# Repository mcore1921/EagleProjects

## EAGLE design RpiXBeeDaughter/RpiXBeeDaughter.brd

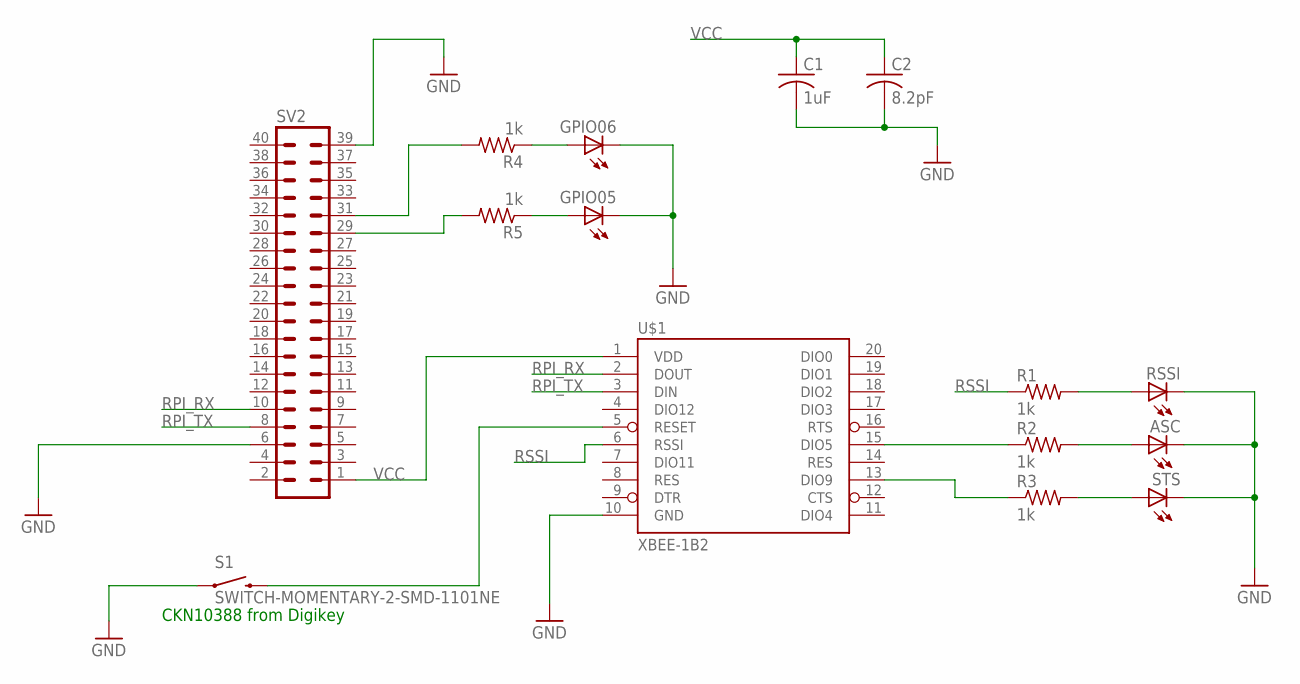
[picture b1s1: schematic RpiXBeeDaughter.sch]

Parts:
ASC: LEDCHIP-LED0603; CHIP-LED0603
C1: 1uF; C0805
C2: 8.2pF; C0603
GPIO05, GPIO06: LEDCHIP-LED0603; CHIP-LED0603
R1, R2, R3, R4, R5: 1k; R0603
RSSI: LEDCHIP-LED0603; CHIP-LED0603
S1: SWITCH-MOMENTARY-2-SMD-1101NE; TACTILE-SWITCH-1101NE
STS: LEDCHIP-LED0603; CHIP-LED0603
SV2: MA20-2
U$1: XBEE-1B2; XBEE-SILK

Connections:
GND: ASC.C, C1.2, C2.2, GPIO05.C, GPIO06.C, RSSI.C, S1.P$1 (1), STS.C, SV2.6, SV2.39, U$1.10 (GND)
unnamed: S1.P$2 (2), U$1.5 (RESET)
unnamed: R3.2, STS.A
unnamed: R2.1, U$1.15 (DIO5)
unnamed: R1.2, RSSI.A
unnamed: ASC.A, R2.2
unnamed: R3.1, U$1.13 (DIO9)
unnamed: R4.2, SV2.31
unnamed: GPIO06.A, R4.1
unnamed: R5.2, SV2.29
unnamed: GPIO05.A, R5.1
RPI_RX: SV2.10, U$1.2 (DOUT)
RPI_TX: SV2.8, U$1.3 (DIN)
RSSI: R1.1, U$1.6 (RSSI)
VCC: C1.1, C2.1, SV2.1, U$1.1 (VDD)

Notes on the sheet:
CKN10388 from Digikey

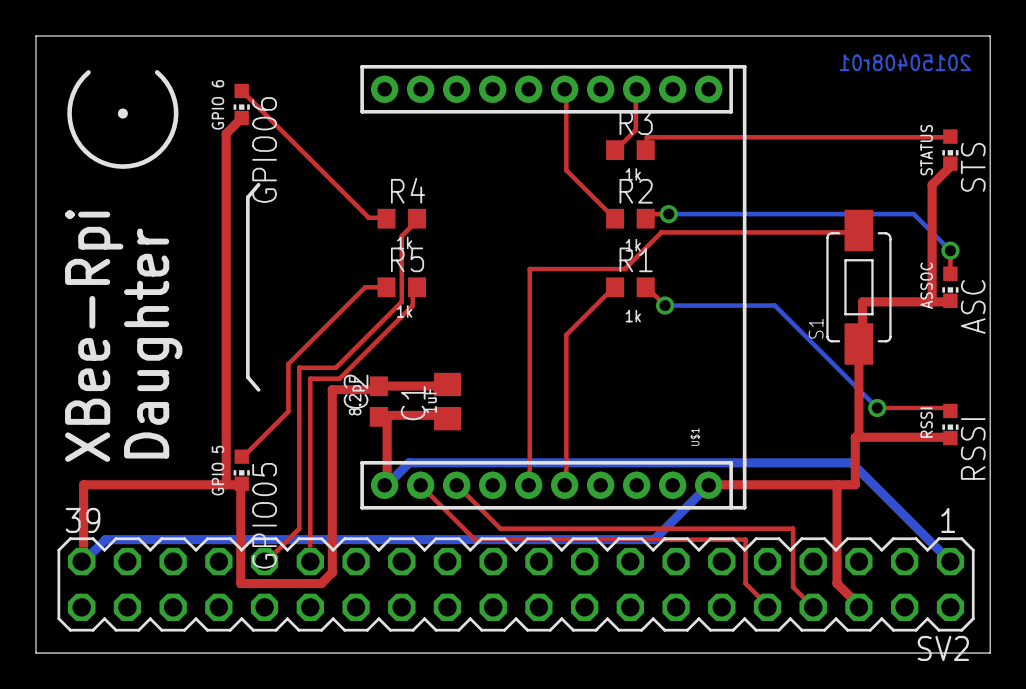
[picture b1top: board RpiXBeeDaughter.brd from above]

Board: 2 copper layers, 53.0 x 34.3 mm, 15 parts (0 on the bottom side), 15 nets.

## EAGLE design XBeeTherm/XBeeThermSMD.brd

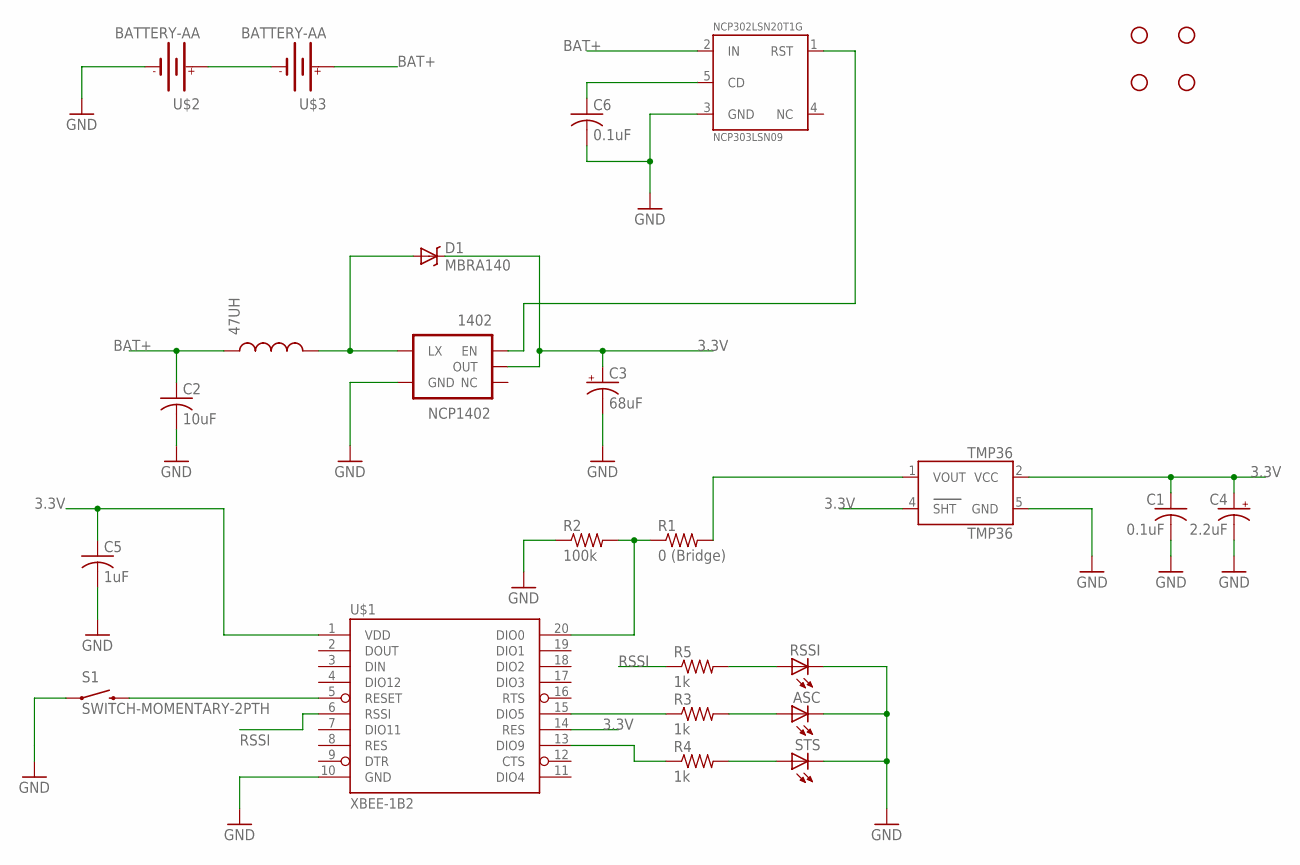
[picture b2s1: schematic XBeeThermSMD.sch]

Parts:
47UH: INDUCTORCR54; CR54
1402: NCP1402; SOT23-5
ASC: LEDCHIP-LED0603; CHIP-LED0603
C1, C6: 0.1uF; C0402
C2: 10uF; C0805
C3: 68uF; CT3216
C4: 2.2uF; R/2012-12R
C5: 1uF; C0805
D1: MBRA140; SMA-DIODE
NCP302LSN20T1G: NCP303LSN09; SOT23-5
R1: 0 (Bridge); R0603
R2: 100k; R0603
R3, R4, R5: 1k; R0603
RSSI: LEDCHIP-LED0603; CHIP-LED0603
S1: SWITCH-MOMENTARY-2PTH; TACTILE-PTH
STANDOFF1, STANDOFF2, STANDOFF3, STANDOFF4: STAND-OFF
STS: LEDCHIP-LED0603; CHIP-LED0603
TMP36: TMP36; SOT23-5
U$1: XBEE-1B2; XBEE-SILK
U$2, U$3: BATTERY-AA; BATTERY_AA_CLIPS

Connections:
3.3V: 1402.2 (OUT), C1.1, C3.+, C4.+, C5.1, D1.C, TMP36.2 (VCC), TMP36.4 (SHT), U$1.1 (VDD), U$1.14 (RES)
BAT+: 47UH.P$1 (1), C2.1, NCP302LSN20T1G.2 (IN), U$3.PWR@1 (+), U$3.PWR@2 (+)
GND: 1402.4 (GND), ASC.C, C1.2, C2.2, C3.-, C4.-, C5.2, C6.2, NCP302LSN20T1G.3 (GND), R2.1, RSSI.C, S1.1, STS.C, TMP36.5 (GND), U$1.10 (GND), U$2.GND@1 (-), U$2.GND@2 (-)
unnamed: 47UH.P$2 (2), 1402.5 (LX), D1.A
unnamed: U$2.PWR@1 (+), U$2.PWR@2 (+), U$3.GND@1 (-), U$3.GND@2 (-)
unnamed: R1.1, R2.2, U$1.20 (DIO0)
unnamed: R1.2, TMP36.1 (VOUT)
unnamed: R3.1, U$1.15 (DIO5)
unnamed: R4.1, U$1.13 (DIO9)
unnamed: ASC.A, R3.2
unnamed: R4.2, STS.A
unnamed: S1.3 (2), U$1.5 (RESET)
unnamed: C6.1, NCP302LSN20T1G.5 (CD)
unnamed: 1402.1 (EN), NCP302LSN20T1G.1 (RST)
unnamed: R5.2, RSSI.A
RSSI: R5.1, U$1.6 (RSSI)

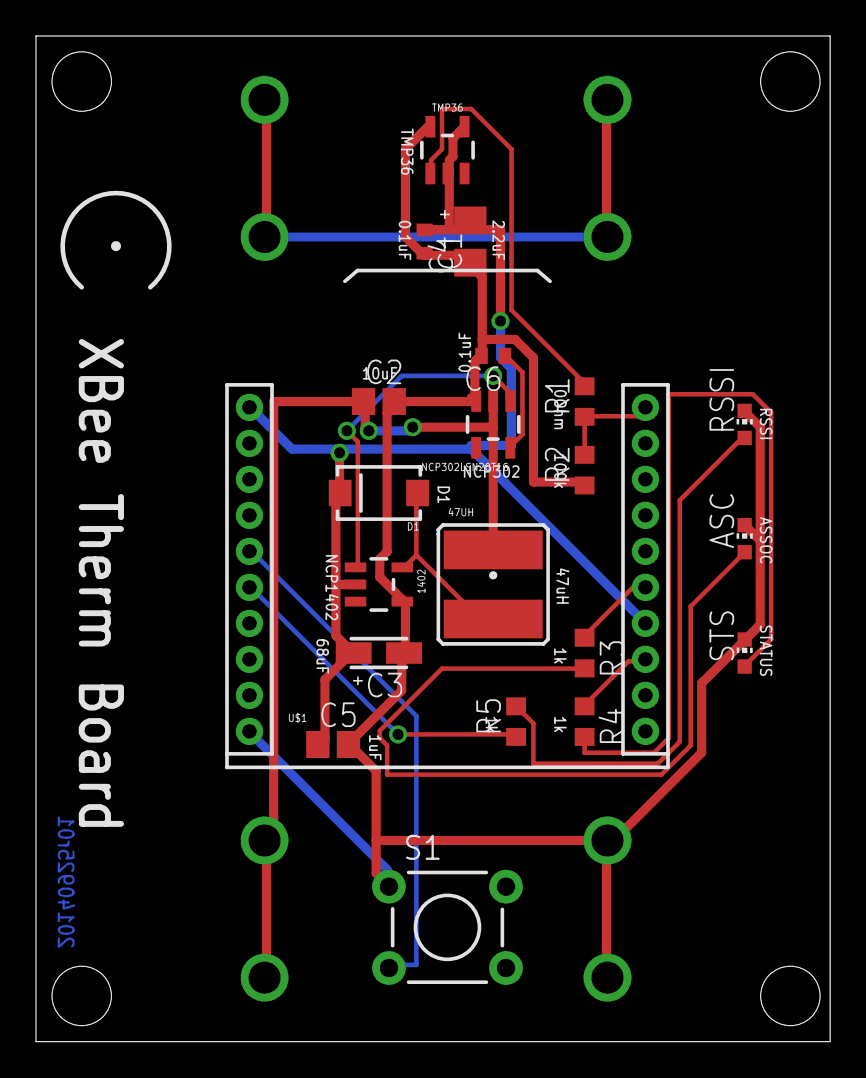
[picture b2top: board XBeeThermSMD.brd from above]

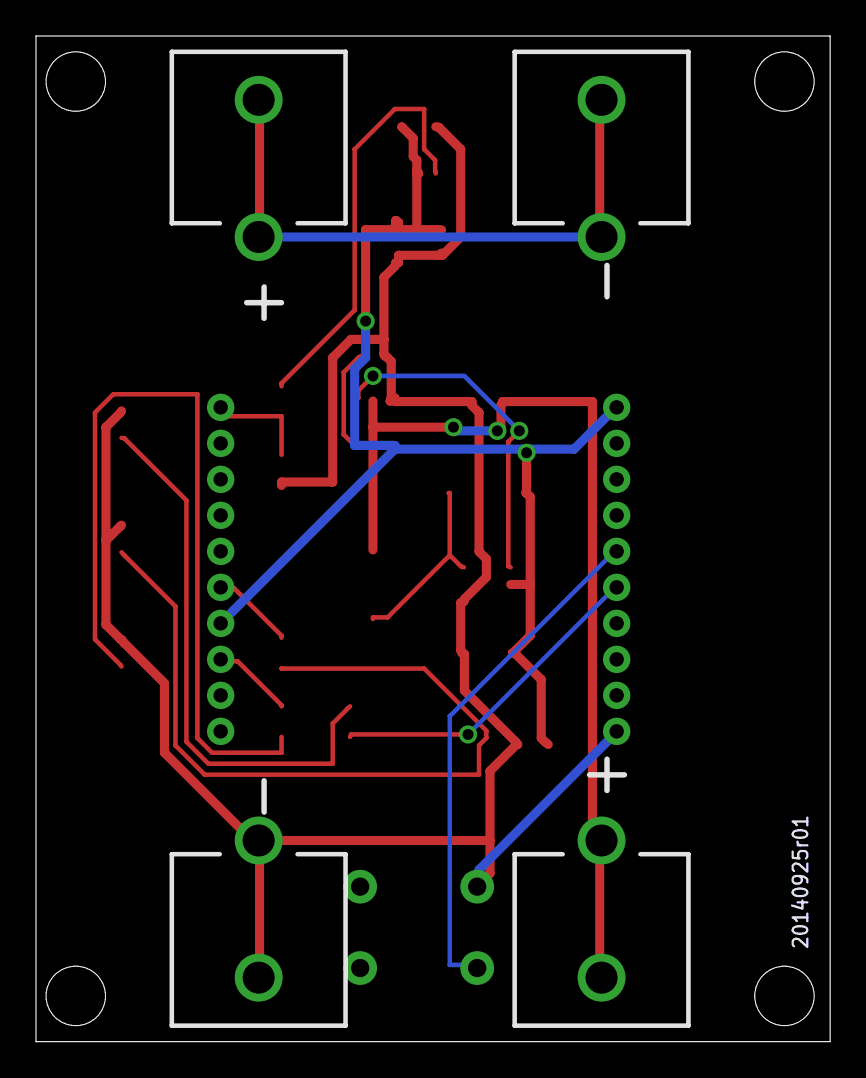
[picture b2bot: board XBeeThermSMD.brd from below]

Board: 2 copper layers, 44.1 x 55.9 mm, 27 parts (2 on the bottom side), 16 nets.

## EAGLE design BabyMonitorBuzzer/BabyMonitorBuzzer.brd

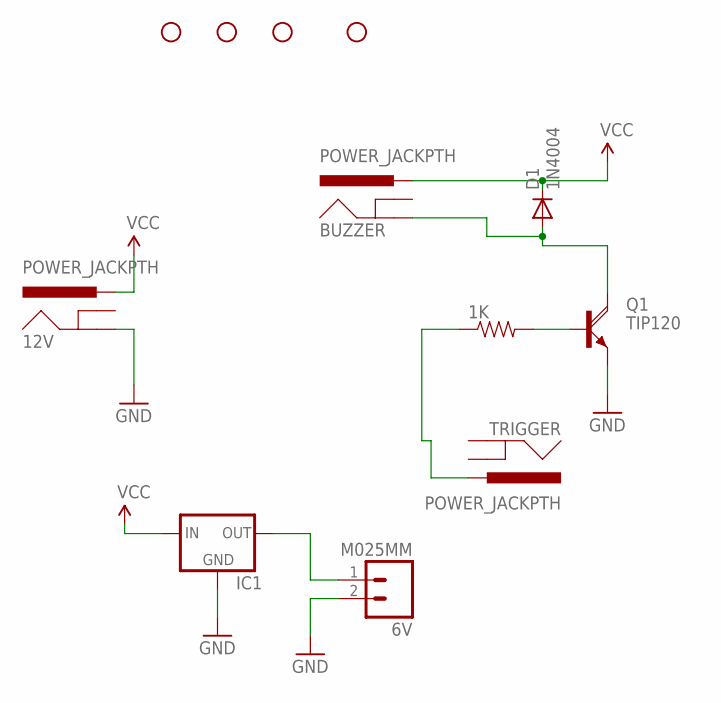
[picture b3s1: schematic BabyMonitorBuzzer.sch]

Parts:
1K: RESISTORAXIAL-0.3; AXIAL-0.3
6V: M025MM; SCREWTERMINAL-5MM-2
12V: POWER_JACKPTH; POWER_JACK_PTH
BUZZER: POWER_JACKPTH; POWER_JACK_PTH
D1: 1N4004; DO41-10
IC1: 78XXL
Q1: TIP120; TO220AH
STANDOFF1, STANDOFF2, STANDOFF3, STANDOFF4: STAND-OFF
TRIGGER: POWER_JACKPTH; POWER_JACK_PTH

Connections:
GND: 6V.2, 12V.GND, IC1.GND, Q1.E
unnamed: 1K.P$2 (2), Q1.B
unnamed: BUZZER.GND, D1.A, Q1.C
unnamed: 1K.P$1 (1), TRIGGER.PWR
unnamed: 6V.1, IC1.OUT
VCC: 12V.PWR, BUZZER.PWR, D1.C, IC1.IN

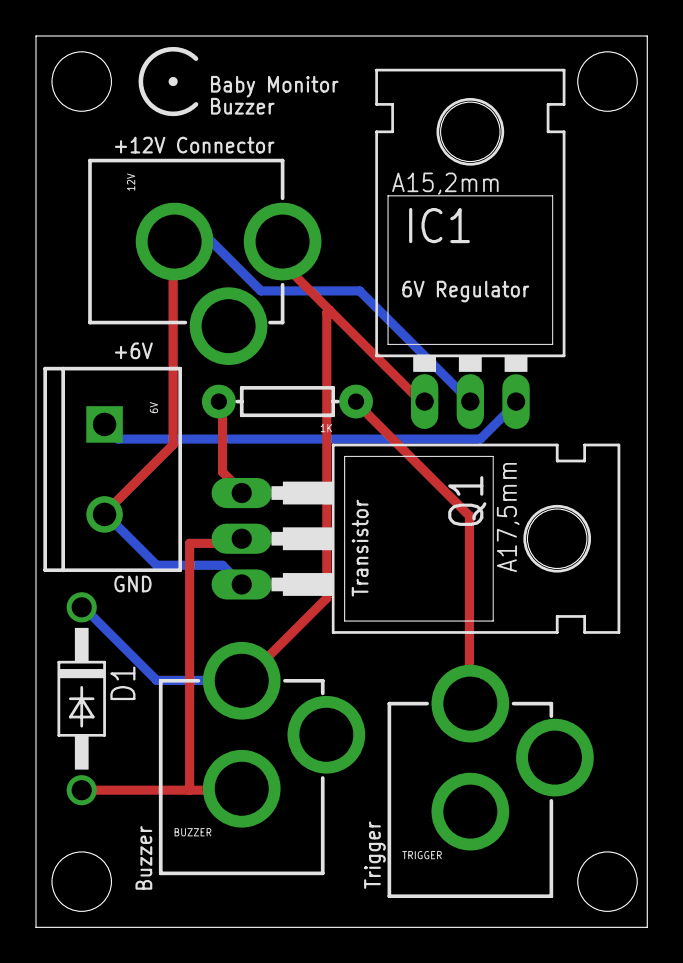
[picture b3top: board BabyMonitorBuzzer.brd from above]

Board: 2 copper layers, 34.0 x 49.5 mm, 12 parts (0 on the bottom side), 6 nets.

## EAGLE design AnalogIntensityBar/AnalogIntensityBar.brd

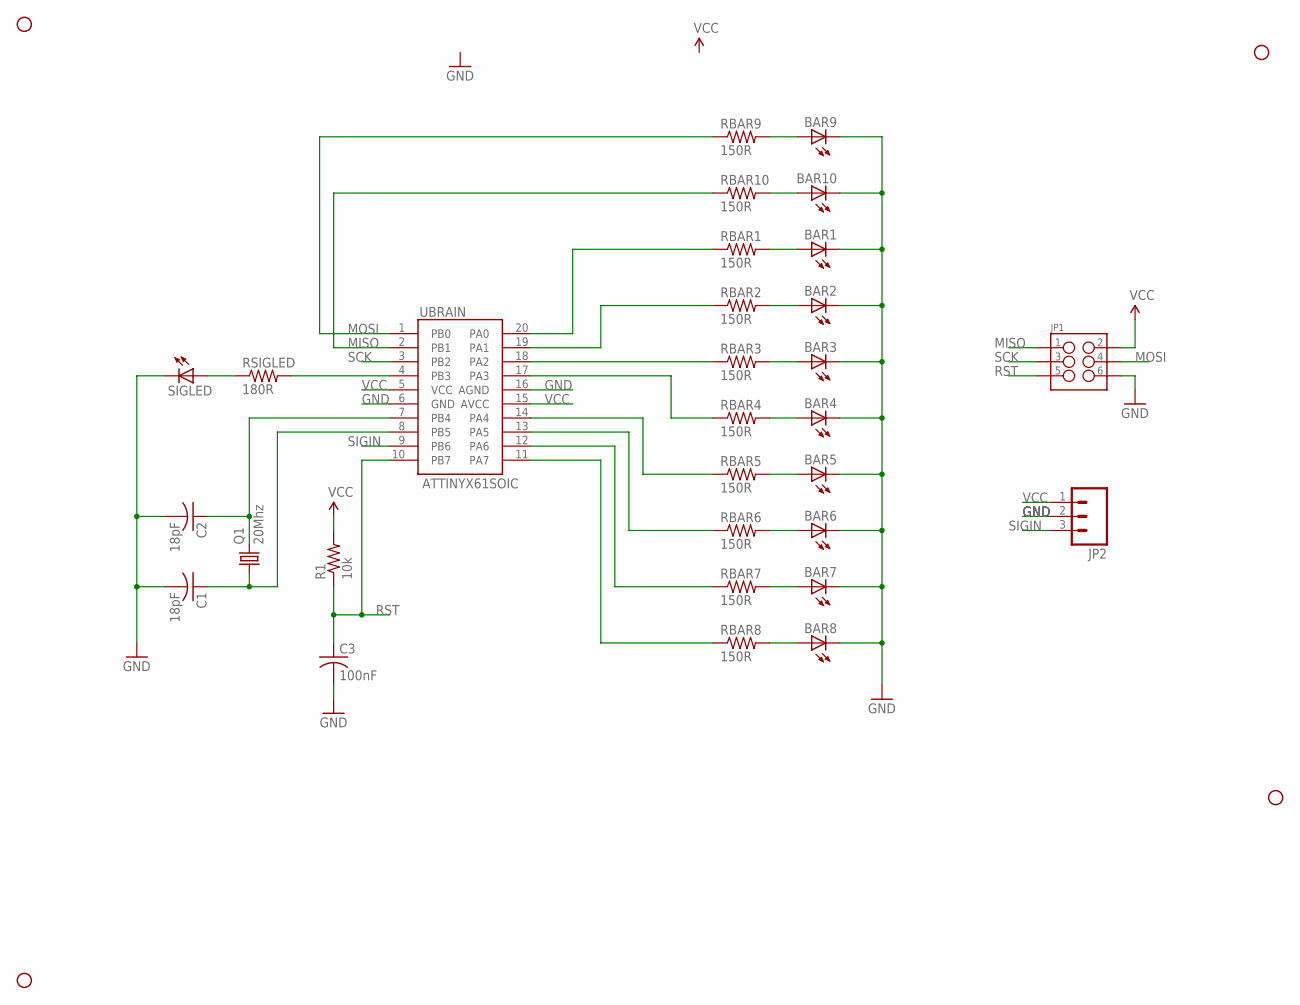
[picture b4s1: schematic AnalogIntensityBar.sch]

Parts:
BAR1, BAR2, BAR3, BAR4, BAR5, BAR6, BAR7, BAR8, BAR9, BAR10: LEDCHIP-LED0603; CHIP-LED0603
C1, C2: 18pF; C0402
C3: 100nF; C0402
JP1: M03X22X3_SILK_SM; 2X3
JP2: M03PTH; 1X03
Q1: 20Mhz; HC49UP
R1: 10k; R0402
RBAR1, RBAR2, RBAR3, RBAR4, RBAR5, RBAR6, RBAR7, RBAR8, RBAR9, RBAR10: 150R; R0603
RSIGLED: 180R; R0603
SIGLED: LEDCHIP-LED0805; CHIP-LED0805
STANDOFF1, STANDOFF2, STANDOFF3, STANDOFF4: STAND-OFF
UBRAIN: ATTINYX61SOIC; 20S2

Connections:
GND: BAR1.C, BAR2.C, BAR3.C, BAR4.C, BAR5.C, BAR6.C, BAR7.C, BAR8.C, BAR9.C, BAR10.C, C1.2, C2.2, C3.2, JP1.6, JP2.2, SIGLED.C, UBRAIN.6 (GND), UBRAIN.16 (AGND)
MISO: JP1.1, RBAR10.1, UBRAIN.2 (PB1)
MOSI: JP1.4, RBAR9.1, UBRAIN.1 (PB0)
unnamed: RBAR1.1, UBRAIN.20 (PA0)
unnamed: RBAR2.1, UBRAIN.19 (PA1)
unnamed: C1.1, Q1.1, UBRAIN.8 (PB5)
unnamed: C2.1, Q1.2, UBRAIN.7 (PB4)
unnamed: RBAR3.1, UBRAIN.18 (PA2)
unnamed: RBAR4.1, UBRAIN.17 (PA3)
unnamed: RBAR5.1, UBRAIN.14 (PA4)
unnamed: RBAR6.1, UBRAIN.13 (PA5)
unnamed: RBAR7.1, UBRAIN.12 (PA6)
unnamed: RBAR8.1, UBRAIN.11 (PA7)
unnamed: BAR1.A, RBAR1.2
unnamed: BAR2.A, RBAR2.2
unnamed: BAR3.A, RBAR3.2
unnamed: BAR4.A, RBAR4.2
unnamed: BAR5.A, RBAR5.2
unnamed: BAR6.A, RBAR6.2
unnamed: BAR7.A, RBAR7.2
unnamed: BAR8.A, RBAR8.2
unnamed: RSIGLED.2, UBRAIN.4 (PB3)
unnamed: RSIGLED.1, SIGLED.A
unnamed: BAR9.A, RBAR9.2
unnamed: BAR10.A, RBAR10.2
RST: C3.1, JP1.5, R1.1, UBRAIN.10 (PB7)
SCK: JP1.3, UBRAIN.3 (PB2)
SIGIN: JP2.3, UBRAIN.9 (PB6)
VCC: JP1.2, JP2.1, R1.2, UBRAIN.5 (VCC), UBRAIN.15 (AVCC)

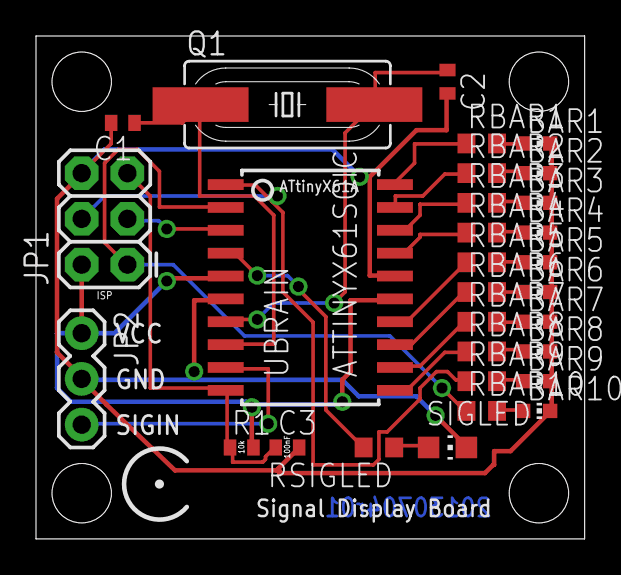
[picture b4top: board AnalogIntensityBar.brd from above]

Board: 2 copper layers, 30.5 x 27.9 mm, 34 parts (0 on the bottom side), 29 nets.

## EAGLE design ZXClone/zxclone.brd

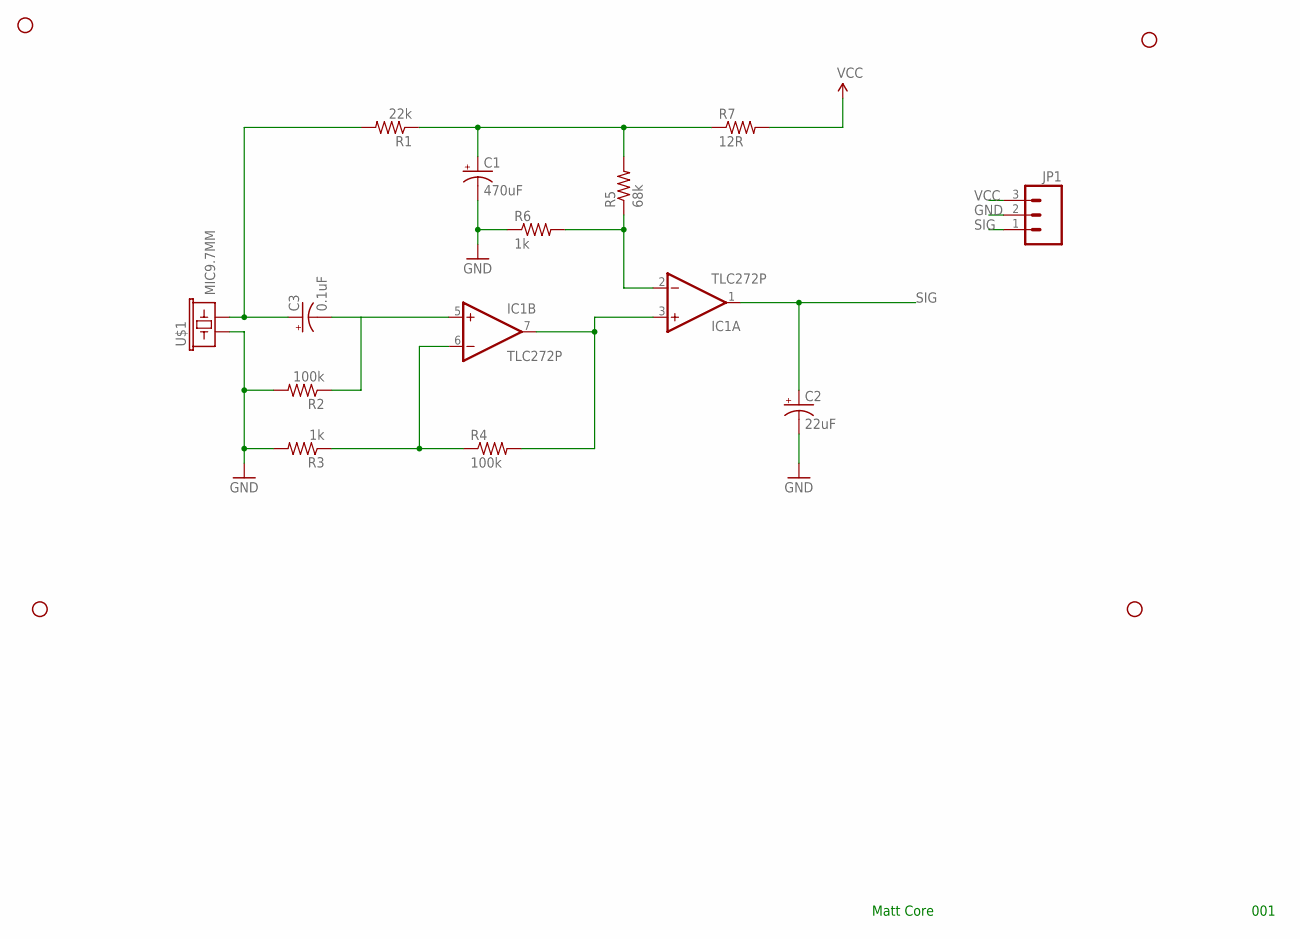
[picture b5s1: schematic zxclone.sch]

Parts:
C1: 470uF; E2,5-7
C2: 22uF; E5-4
C3: 0.1uF; E1,8-4
IC1: TLC272P; DIL08
JP1: M03PTH; 1X03
R1: 22k; 0207/10
R2, R4: 100k; 0207/10
R3, R6: 1k; 0207/10
R5: 68k; 0207/10
R7: 12R; 0207/10
STANDOFF1, STANDOFF2, STANDOFF3, STANDOFF4: STAND-OFF
U$1: MIC9.7MM; MIC-9.7MM

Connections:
GND: C1.-, C2.-, JP1.2, R2.2, R3.2, R6.1, U$1.1
unnamed: C1.+, R1.1, R5.2, R7.1
unnamed: IC1.2 (-IN), R5.1, R6.2
unnamed: IC1.3 (+IN), IC1.7 (OUT), R4.2
unnamed: IC1.6 (-IN), R3.1, R4.1
unnamed: C3.-, IC1.5 (+IN), R2.1
unnamed: C3.+, R1.2, U$1.2
SIG: C2.+, IC1.1 (OUT), JP1.1
V+: IC1.8 (V+)
V-: IC1.4 (V-)
VCC: JP1.3, R7.2

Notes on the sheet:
Matt Core
001

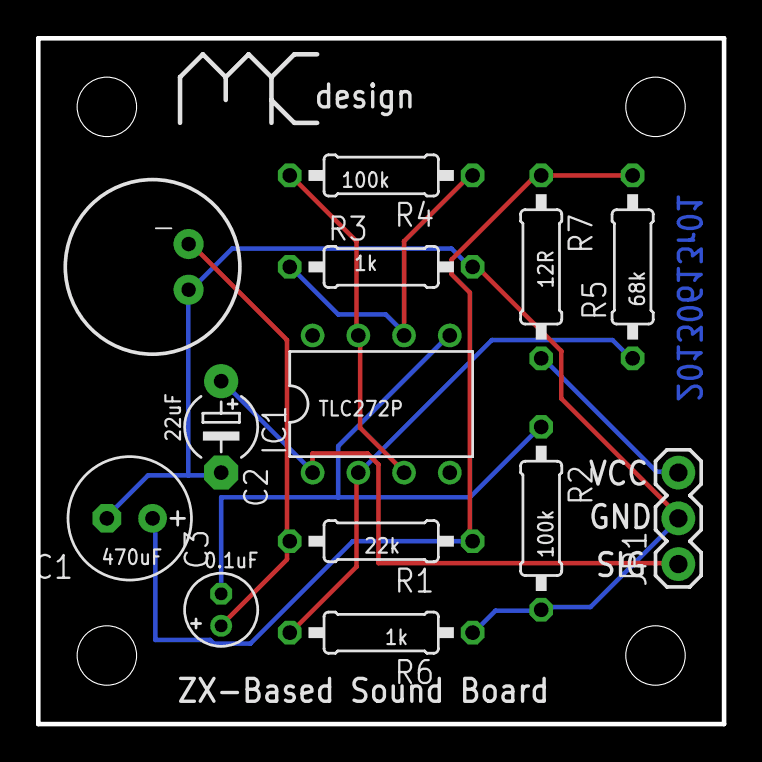
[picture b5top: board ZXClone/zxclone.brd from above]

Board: 2 copper layers, 38.1 x 38.1 mm, 17 parts (0 on the bottom side), 9 nets.

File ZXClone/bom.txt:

Partlist exported from C:/Users/Matt/Documents/eagle/ZXClone/zxclone.sch at 7/21/2013 9:11:37 PM

Part      Value     Device        Package   Description                                                    
C1        470uF     CPOL-USE2.5-7 E2,5-7    POLARIZED CAPACITOR, American symbol                           
C2        22uF      CPOL-USE5-4   E5-4      POLARIZED CAPACITOR, American symbol                           
C3        0.1uF     CPOL-USE1.8-4 E1,8-4    POLARIZED CAPACITOR, American symbol                           
IC1       TLC272P   TLC272P       DIL08     OP AMP                                                         
JP1                 M03PTH        1X03      Header 3                                                       
R1        22k       R-US_0207/10  0207/10   RESISTOR, American symbol                                      
R2        100k      R-US_0207/10  0207/10   RESISTOR, American symbol                                      
R3        1k        R-US_0207/10  0207/10   RESISTOR, American symbol                                      
R4        100k      R-US_0207/10  0207/10   RESISTOR, American symbol                                      
R5        68k       R-US_0207/10  0207/10   RESISTOR, American symbol                                      
R6        1k        R-US_0207/10  0207/10   RESISTOR, American symbol                                      
R7        12R       R-US_0207/10  0207/10   RESISTOR, American symbol                                      
STANDOFF1 STAND-OFF STAND-OFF     STAND-OFF #4 Stand Off                                                   
STANDOFF2 STAND-OFF STAND-OFF     STAND-OFF #4 Stand Off                                                   
STANDOFF3 STAND-OFF STAND-OFF     STAND-OFF #4 Stand Off                                                   
STANDOFF4 STAND-OFF STAND-OFF     STAND-OFF #4 Stand Off                                                   
U$1       MIC9.7MM  MIC9.7MM      MIC-9.7MM Omni-directional electret microphone. 9.7mm standard diameter.

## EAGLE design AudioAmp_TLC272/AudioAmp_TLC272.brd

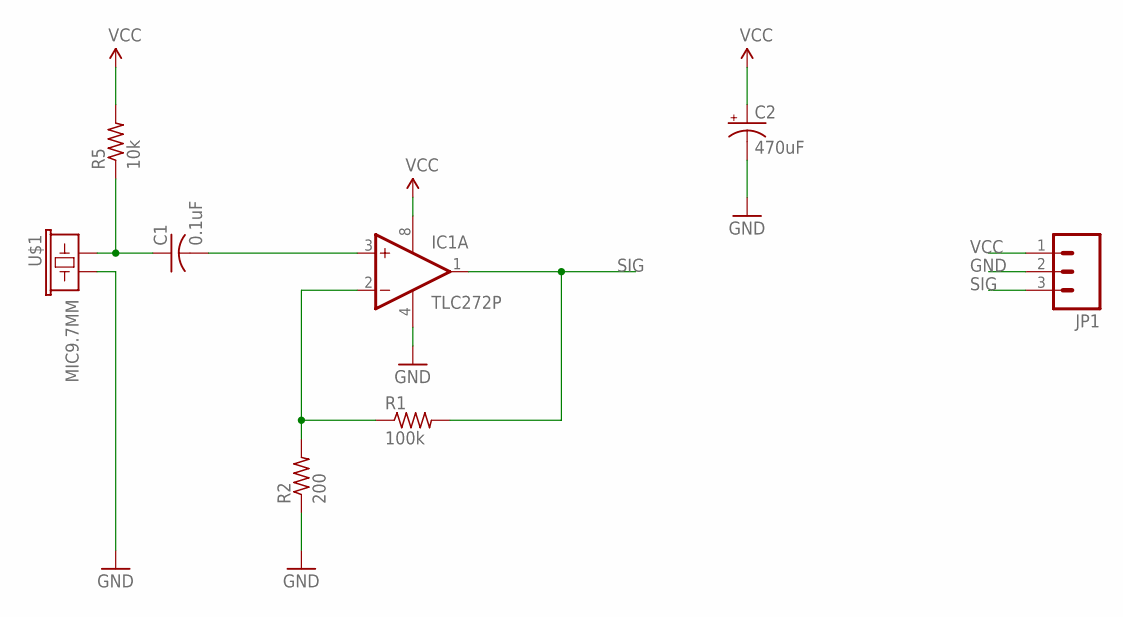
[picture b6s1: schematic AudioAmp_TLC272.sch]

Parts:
C1: 0.1uF; C025-025X050
C2: 470uF; E2,5-7
IC1: TLC272P; DIL08
JP1: M03PTH; 1X03
R1: 100k; 0207/10
R2: 200; 0207/10
R5: 10k; 0207/10
U$1: MIC9.7MM; MIC-9.7MM

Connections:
GND: C2.-, IC1.4 (V-), JP1.2, R2.1, U$1.2
unnamed: C1.1, R5.1, U$1.1
unnamed: C1.2, IC1.3 (+IN)
unnamed: IC1.2 (-IN), R1.1, R2.2
SIG: IC1.1 (OUT), JP1.3, R1.2
VCC: C2.+, IC1.8 (V+), JP1.1, R5.2

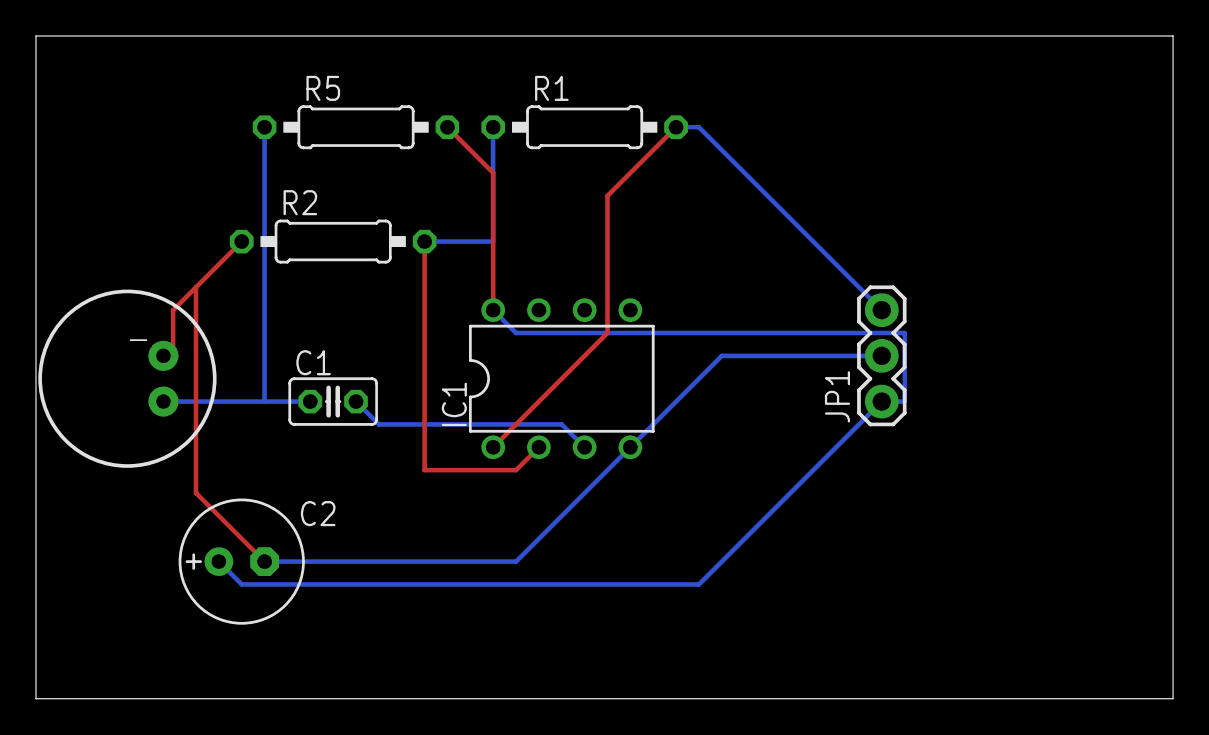
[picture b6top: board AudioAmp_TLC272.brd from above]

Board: 2 copper layers, 63.2 x 36.8 mm, 8 parts (0 on the bottom side), 6 nets.

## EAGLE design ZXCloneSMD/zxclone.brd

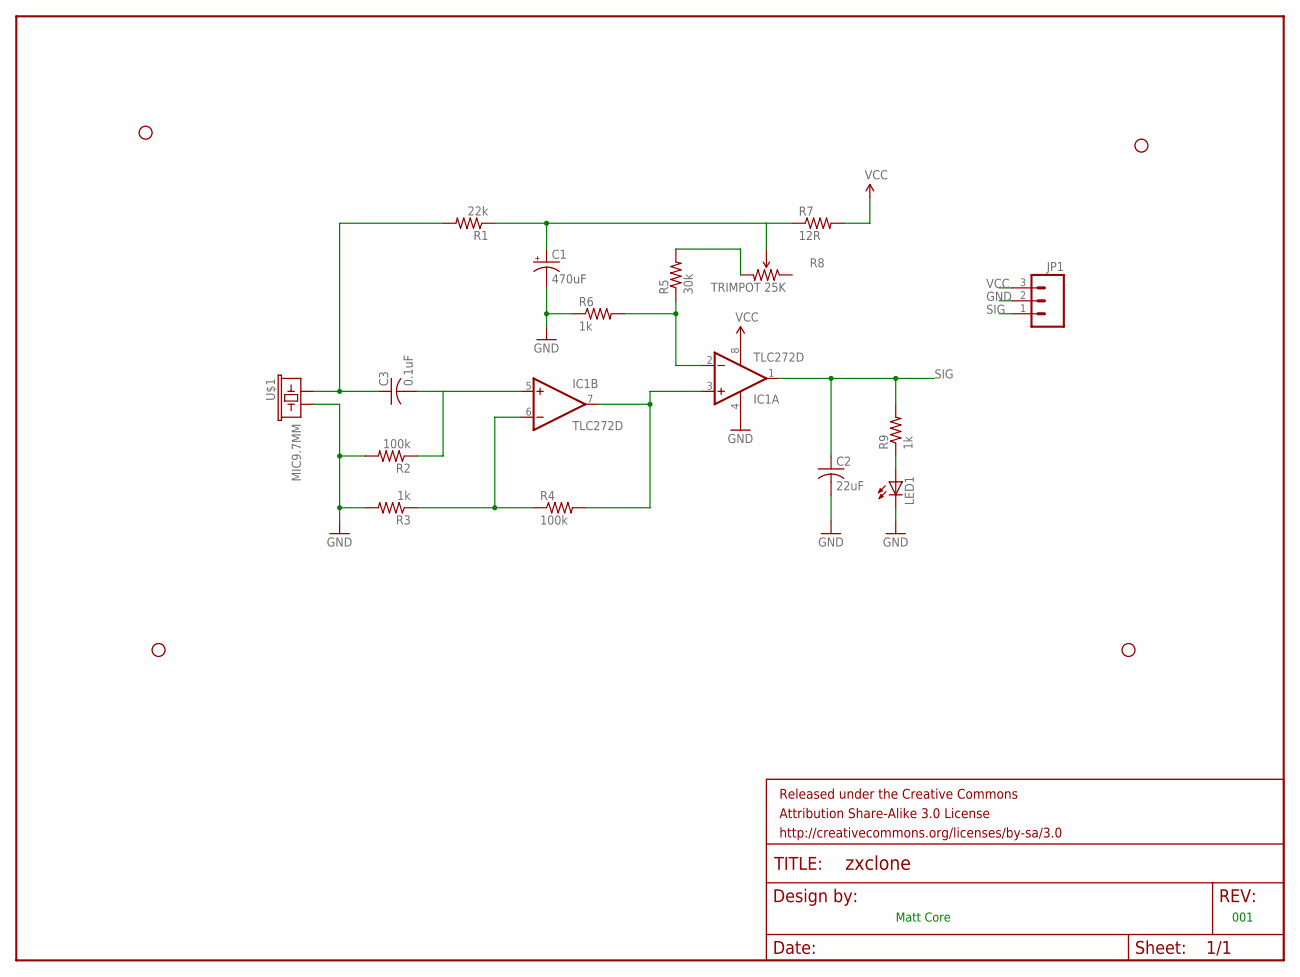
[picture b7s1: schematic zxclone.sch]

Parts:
C1: 470uF; E2,5-7
C2: 22uF; C1206
C3: 0.1uF; C1005
FRAME1: FRAME-LETTER; CREATIVE_COMMONS
IC1: TLC272D; SO08
JP1: M03PTH; 1X03
LED1: LEDSML0603; SML0603
R1: 22k; R0402
R2, R4: 100k; R0402
R3, R6, R9: 1k; R0402
R5: 30k; R0402
R7: 12R; R0805
R8: TRIMPOT 25K; TRIMPOT_TC33
STANDOFF1, STANDOFF2, STANDOFF3, STANDOFF4: STAND-OFF
U$1: MIC9.7MM; MIC-9.7MM

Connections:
GND: C1.-, C2.2, IC1.4 (V-), JP1.2, LED1.C, R2.2, R3.2, R6.1, U$1.2
unnamed: C1.+, R1.1, R7.1, R8.2 (WIPER)
unnamed: IC1.2 (-IN), R5.1, R6.2
unnamed: IC1.3 (+IN), IC1.7 (OUT), R4.2
unnamed: IC1.6 (-IN), R3.1, R4.1
unnamed: C3.2, IC1.5 (+IN), R2.1
unnamed: R5.2, R8.3 (CW)
unnamed: C3.1, R1.2, U$1.1
unnamed: LED1.A, R9.1
SIG: C2.1, IC1.1 (OUT), JP1.1, R9.2
VCC: IC1.8 (V+), JP1.3, R7.2

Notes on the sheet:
Matt Core
001

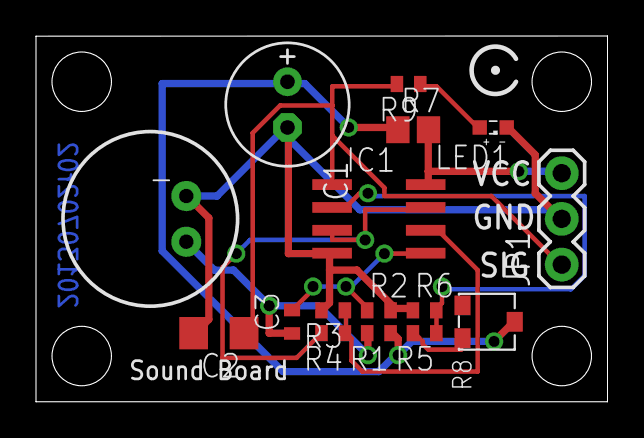
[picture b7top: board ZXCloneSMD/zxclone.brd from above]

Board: 2 copper layers, 31.8 x 20.3 mm, 21 parts (0 on the bottom side), 11 nets.

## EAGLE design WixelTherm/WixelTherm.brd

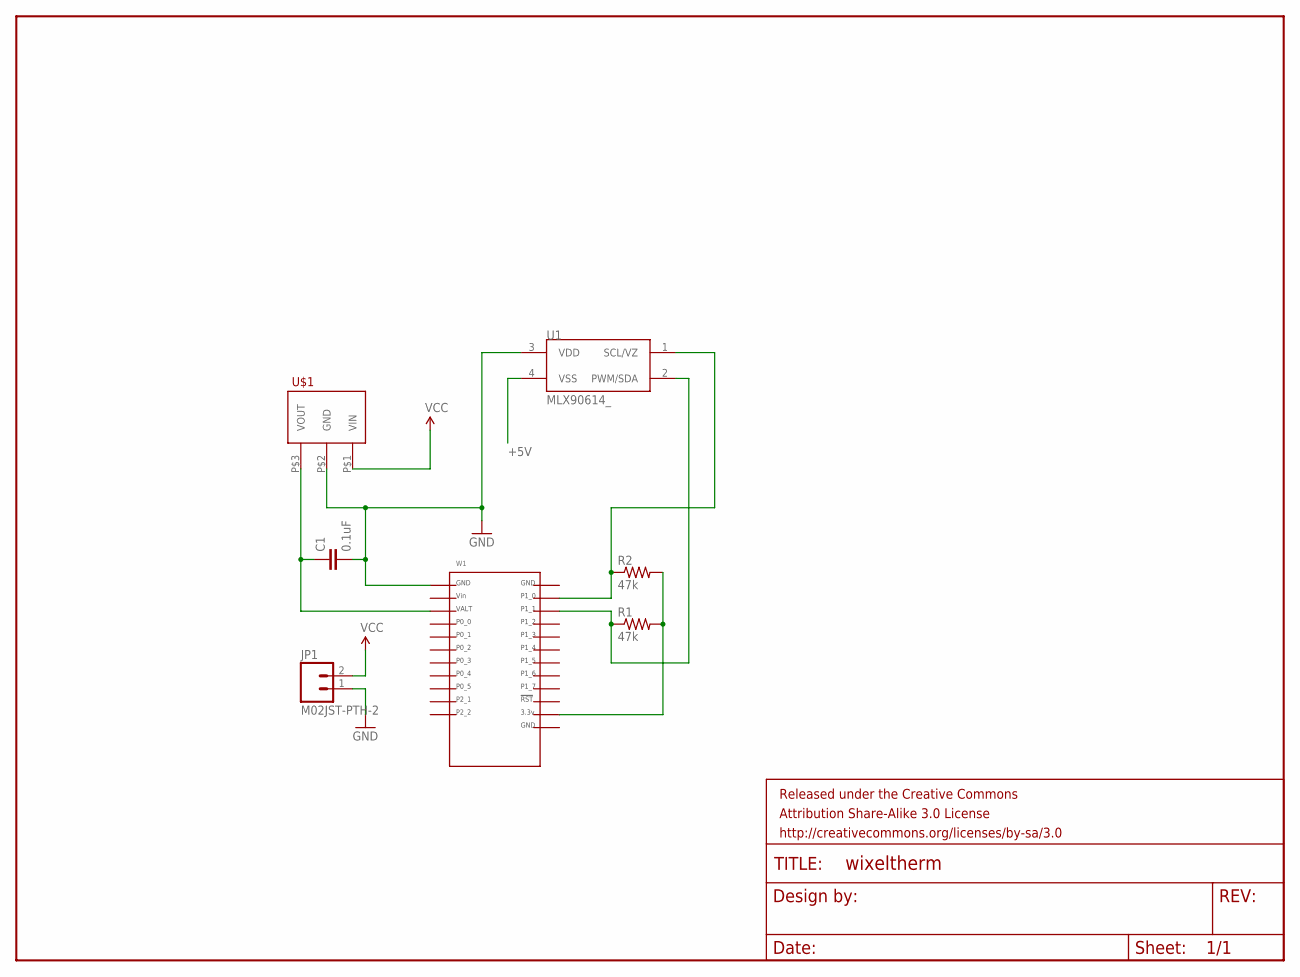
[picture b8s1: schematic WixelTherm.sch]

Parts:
C1: 0.1uF; 0603-CAP
FRAME1: FRAME-LETTER; CREATIVE_COMMONS
JP1: M02JST-PTH-2; JST-2-PTH
R1, R2: 47k; 0207/10
U1: MLX90614_; TO-39
U$1: POLOLU_NCP1402; POLOLU_BREAKOUT
W1: WIXEL

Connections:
+5V: C1.1, U1.4 (VSS), U$1.P$3 (VOUT), W1.P$3
GND: C1.2, JP1.1, U1.3 (VDD), U$1.P$2 (GND), W1.P$1
unnamed: R1.1, U1.2 (PWM/SDA), W1.P$14
unnamed: R1.2, R2.2, W1.P$22
unnamed: R2.1, U1.1 (SCL/VZ), W1.P$13
VCC: JP1.2, U$1.P$1 (VIN)

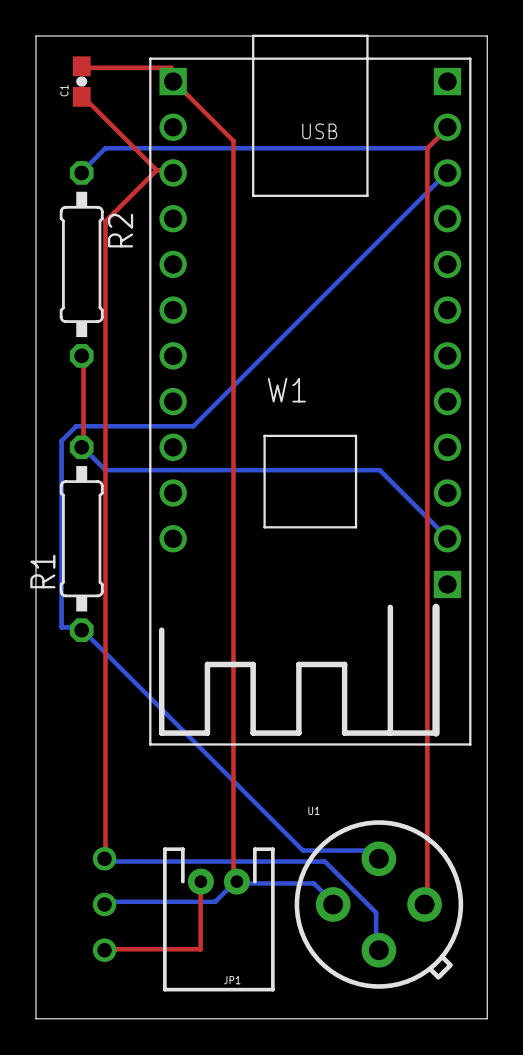
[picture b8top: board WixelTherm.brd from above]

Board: 2 copper layers, 25.1 x 54.6 mm, 8 parts (0 on the bottom side), 6 nets.

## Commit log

2013-06-06 creation
2013-06-12 interim checkin while building schematic
2013-06-12 interim checkin while building zxclone
2013-06-12 another initial rev
2013-06-12 Ready to send gerber files
2013-06-12 revision sent for first fab
2013-06-13 first rev of smd version
2013-07-02 On the way to a second proto board
2013-07-02 Some file cleanup
2013-07-02 Working revision with LED and trimpot
2013-07-03 Second submission for fab to osh park
2013-07-05 First pass of AnalogIntensityBar - still needs top soldermask tuning
2013-07-21 Cleanup
2013-08-18 Early revision (not yet final) of XBee therm board
2013-08-20 First fab of the XBee therm board
2014-03-09 Add BabyMonitorBuzzer project; add a bom text file to XBeeTherm
2014-03-09 Update for the 0 ohm jumper change to the board
2014-09-26 Adding battery undervoltage protection
2015-04-07 Catching up with a lot of changes
2015-04-08 First rev of RpiXBeeDaughter

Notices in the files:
parts and their libraries:
SparkFun-Connectors: Licensing: CC v3.0 Share-Alike You are welcome to use this library for commercial purposes.
SparkFun-Aesthetics: Released under the Creative Commons Attribution Share-Alike 3.0 License
SparkFun-Aesthetics: http://creativecommons.org/licenses/by-sa/3.0
